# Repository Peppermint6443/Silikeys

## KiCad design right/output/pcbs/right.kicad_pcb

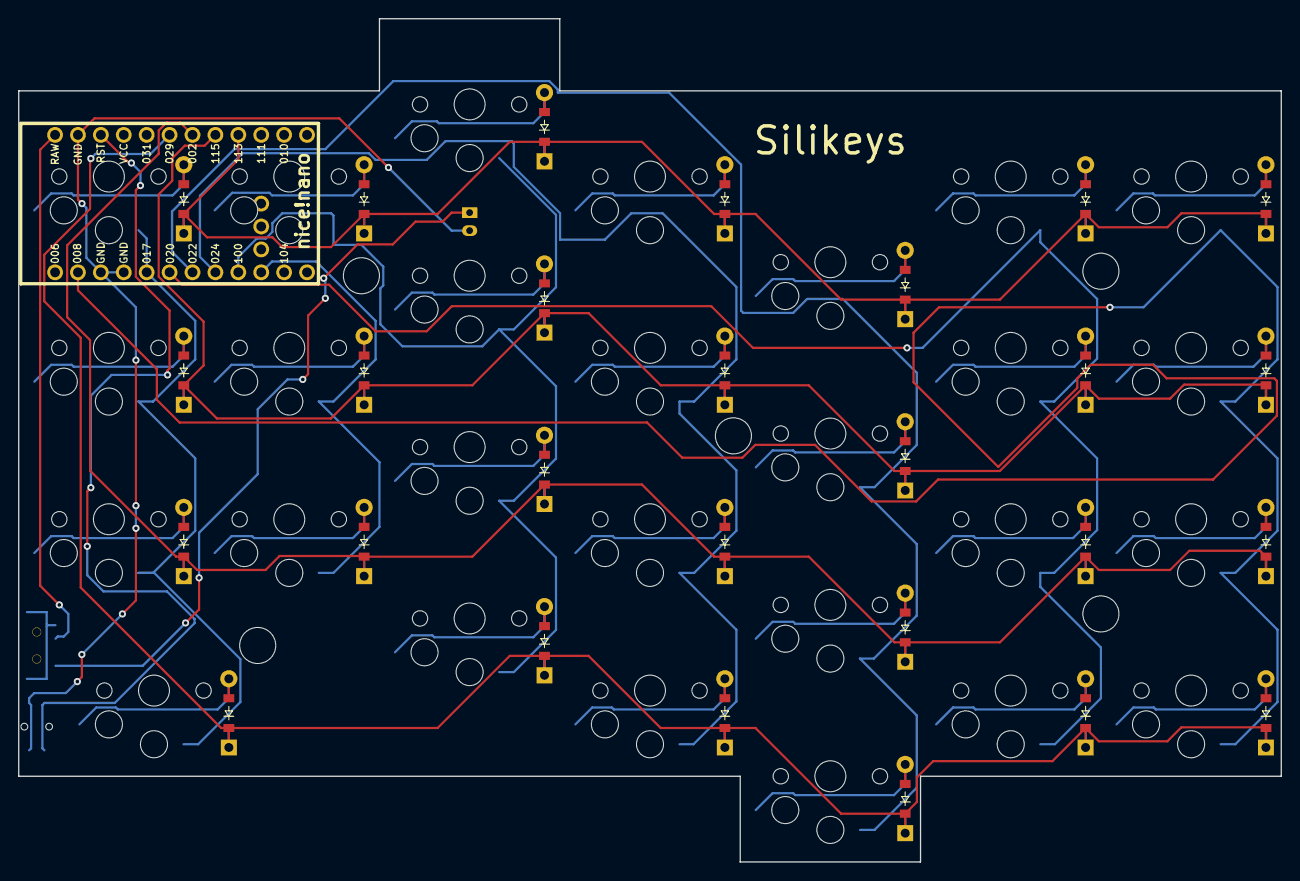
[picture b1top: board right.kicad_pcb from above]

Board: 2 copper layers, 140.0 x 93.5 mm, 58 parts (0 on the bottom side), 42 nets.

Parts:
B1: Panasonic_EVQPUL_EVQPUC
D1, D2, D3, D4, D5, D6, D7, D8, D9, D10, D11, D12, D13, D14, D15, D16, D17, D18, D19, D20, D21, D22, D23, D24, D25, D26, D27: ComboDiode
JST1: JST_PH_S2B-PH-K_02x2.00mm_Angled
MCU1: nice_nano
S1, S2, S3, S4, S5, S6, S7, S8, S9, S10, S11, S12, S13, S14, S15, S16, S17, S18, S19, S20, S21, S22, S23, S24, S25, S26, S27: PG1350
T1: SPDT_C128955

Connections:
GND: B1.1, JST1.2, MCU1.3, MCU1.4, MCU1.23
P002: D1.1, D5.1, D9.1, D13.1, D17.1, D21.1, D25.1, MCU1.18
P008: MCU1.2, S24.1, S25.1, S26.1, S27.1
P011: MCU1.10, S5.1, S6.1, S7.1
P017: MCU1.5, S1.1, S2.1, S3.1, S4.1
P020: MCU1.6, S20.1, S21.1, S22.1, S23.1
P022: MCU1.7, S16.1, S17.1, S18.1, S19.1
P024: MCU1.8, S12.1, S13.1, S14.1, S15.1
P029: D4.1, D8.1, D12.1, D16.1, D20.1, D24.1, MCU1.19
P100: MCU1.9, S8.1, S9.1, S10.1, S11.1
P113: D3.1, D7.1, D11.1, D15.1, D19.1, D23.1, D27.1, MCU1.16
P115: D2.1, D6.1, D10.1, D14.1, D18.1, D22.1, D26.1, MCU1.17
RAW: MCU1.24, T1.2
RST: B1.2, MCU1.22
apos_down: D21.2, S21.2
apos_home: D22.2, S22.2
apos_up: D23.2, S23.2
apos_utility: D20.2, S20.2
enter_down: D25.2, S25.2
enter_home: D26.2, S26.2
enter_up: D27.2, S27.2
enter_utility: D24.2, S24.2
h_anchor: D4.2, S4.2
h_down: D1.2, S1.2
h_home: D2.2, S2.2
h_up: D3.2, S3.2
j_down: D5.2, S5.2
j_home: D6.2, S6.2
j_up: D7.2, S7.2
k_down: D9.2, S9.2
k_home: D10.2, S10.2
k_up: D11.2, S11.2
k_utility: D8.2, S8.2
l_down: D13.2, S13.2
l_home: D14.2, S14.2
l_up: D15.2, S15.2
l_utility: D12.2, S12.2
pos: JST1.1, T1.1
semi_down: D17.2, S17.2
semi_home: D18.2, S18.2
semi_up: D19.2, S19.2
semi_utility: D16.2, S16.2

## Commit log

2025-01-15 initial commit, adding my files to the new repository
2025-01-15 started the new pcb for the left side
2025-01-17 added right, numbers, and altered left a little bit. I tweaked the location of the nice nano, all need to be retraced
2025-01-17 remove all pcb files for a clean slate
